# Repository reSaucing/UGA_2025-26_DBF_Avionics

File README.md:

# UGA_2025-26_DBF_Avionics
UGA 2025/26 avionics section code repo

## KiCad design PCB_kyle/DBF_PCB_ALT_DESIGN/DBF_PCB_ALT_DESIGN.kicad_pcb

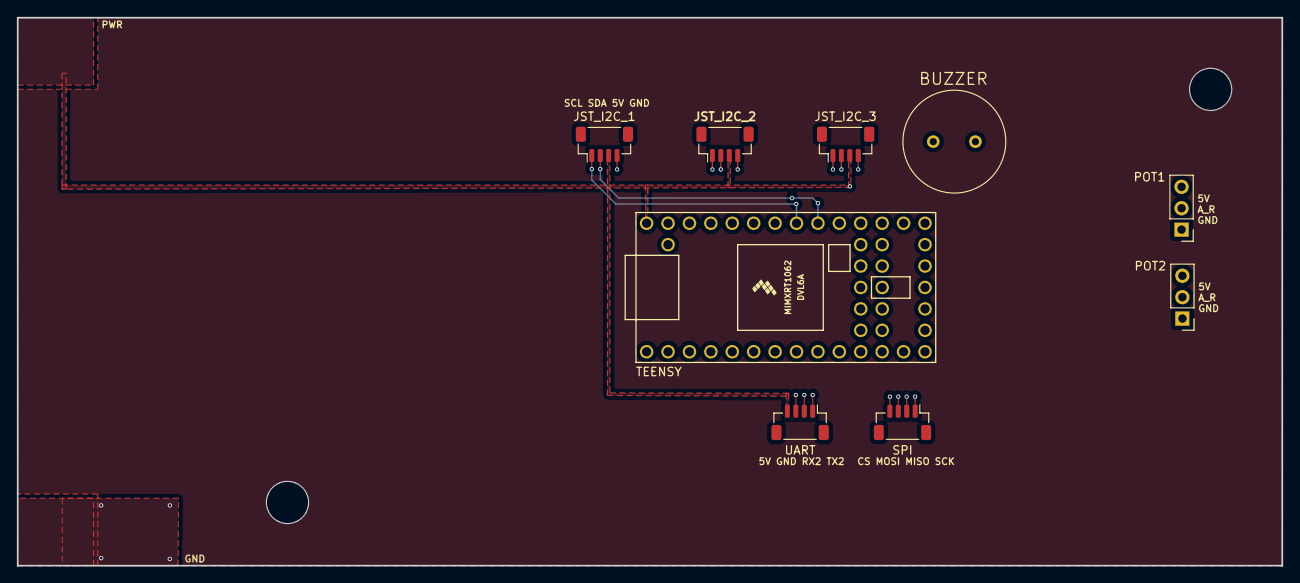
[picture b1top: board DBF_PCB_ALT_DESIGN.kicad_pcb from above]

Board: 4 copper layers, 150.0 x 65.0 mm, 9 parts (0 on the bottom side), 13 nets.

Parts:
BUZZER: XDCR_PS1240P02BT
JST_I2C_1, JST_I2C_2, JST_I2C_3: JST_SH_BM04B-SRSS-TB_1x04-1MP_P1.00mm_Vertical
POT1: POT1; PinHeader_1x03_P2.54mm_Vertical
POT2: PinHeader_1x03_P2.54mm_Vertical
SPI: JST_SH_BM04B-SRSS-TB_1x04-1MP_P1.00mm_Vertical
TEENSY: Teensy 4.0; Teensy40
UART: JST_SH_BM04B-SRSS-TB_1x04-1MP_P1.00mm_Vertical

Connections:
5V_PWR: JST_I2C_1.3, JST_I2C_2.3, JST_I2C_3.3, POT1.3, POT2.3, TEENSY.33, UART.4
CS: SPI.4, TEENSY.12
GND: BUZZER.2, JST_I2C_1.4, JST_I2C_2.4, JST_I2C_3.4, POT1.1, POT2.1, TEENSY.1, TEENSY.32, UART.3
MISO: SPI.2, TEENSY.14
MOSI: SPI.3, TEENSY.13
POT1: POT1.2, TEENSY.22
POT2: POT2.2, TEENSY.21
RX2: TEENSY.9, UART.2
SCK: SPI.1, TEENSY.20
SCL0: JST_I2C_1.1, JST_I2C_2.1, JST_I2C_3.1, TEENSY.26
SDA0: JST_I2C_1.2, JST_I2C_2.2, JST_I2C_3.2, TEENSY.25
TX2: TEENSY.10, UART.1
buzzer: BUZZER.1, TEENSY.23

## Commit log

2025-09-27 updated BMP to store in sdcard
2025-10-08 full sensor array code
2025-10-08 updated comments
2025-10-09 version 1.0 final for testing
2025-10-09 version 1.0 final final for testing
2025-10-09 minor debugging
2025-10-09 testing and debugging
2025-10-11 getting there
2025-10-12 updated trees
2025-10-14 new test programs for classes to improve modularity
2025-10-14 new test programs for aspd
2025-10-14 reorganized
2025-10-14 created master file
2025-10-14 reorganization
2025-10-15 Create TestPotentiometer
2025-10-15 Rename TestPotentiometer to TestPotentiometer.ino
2025-10-15 Update and rename TestPotentiometer.ino to test
2025-10-15 data write updates
2025-10-15 made ASPDClassTest write sensor readings to SD card
2025-10-19 testing and debug of BMP and BNO classes
2025-10-19 comments to aspd class files
2025-10-19 minor file updates
2025-10-19 class file updates for SD card
2025-10-19 started main file
2025-10-19 comments to sd data read
2025-10-19 created the complete array test code. should be working
2025-10-19 forgot if i pushed
2025-10-19 retrieve sensor data finished. thank gemini for all that code.
2025-10-19 minor updates
2025-10-19 added pot adc values to complete test
2025-10-22 fixed airspeed sensor data writing program
2025-10-28 aspd testing debugging
2025-10-28 final review before testing hopefully
2025-10-28 minor udpates
2025-10-29 My alternative PCB design
2025-11-01 tracing almost complete(?)
2025-11-01 DRC errors gone
2025-11-04 Create Potentiometer Value
2025-11-05 pots
2025-11-05 added pot value to angle translation
2025-11-10 added code for truck test
2025-11-12 truck test debugging
2025-11-12 airspeed is working?
2025-11-12 accelerometer working
2025-11-16 Updated DBF_PCB_ALT_DESIGN
2025-11-17 should be the final thingy
2025-11-17 Changed the hole sizes to an M5 screw size
2025-11-17 Pin headers changed + no DRC errors, some warnings not too bad
2025-11-17 No big changes
2025-11-17 finally aspd working??
2025-11-18 gps test code
2026-01-27 fianal final
2026-01-30 restructured finalfinal folder
2026-01-30 copy of finalfinal for truck test
2026-01-31 added script to transfer data to computer
2026-02-11 save file script is tested and works now
2026-02-25 Added beeper function and replaced error print statements with beeper function calls
